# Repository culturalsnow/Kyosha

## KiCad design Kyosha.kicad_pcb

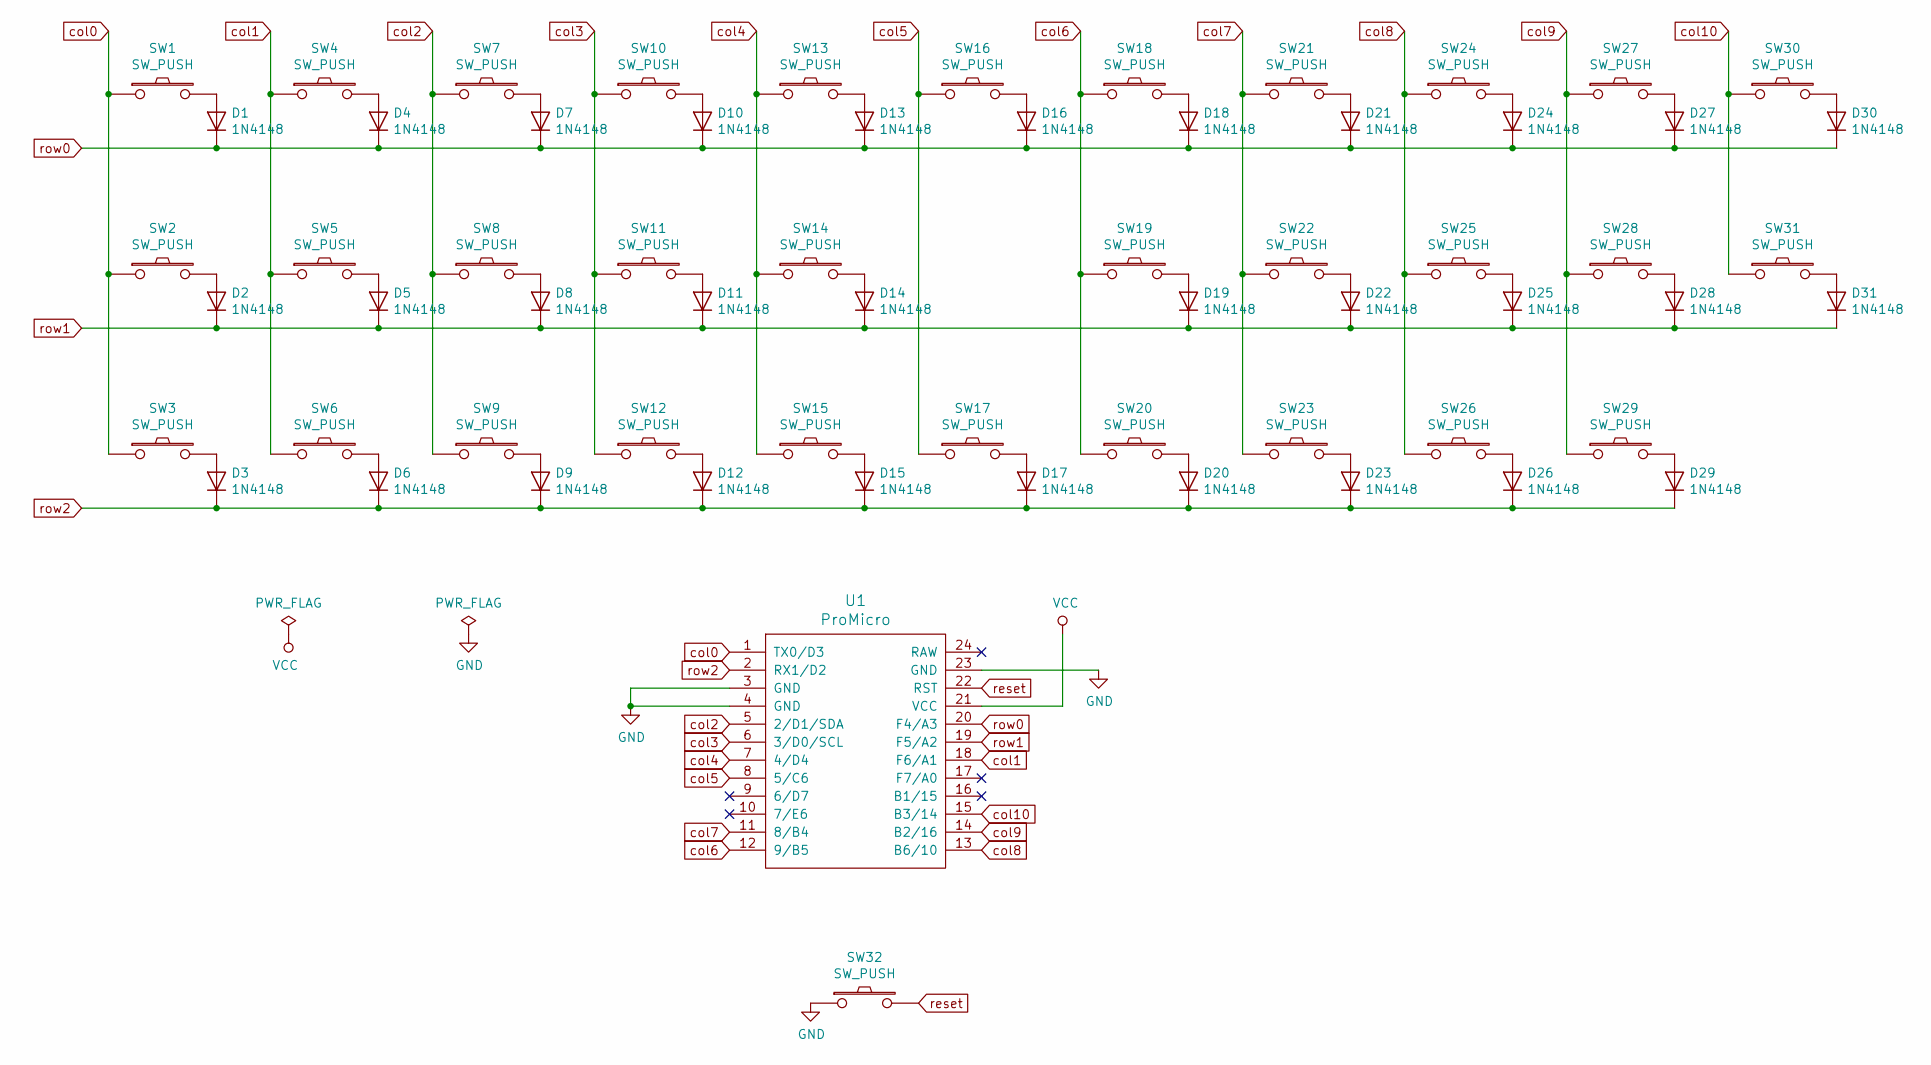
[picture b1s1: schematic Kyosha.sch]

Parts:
D1, D2, D3, D4, D5, D6, D7, D8, D9, D10, D11, D12, D13, D14, D15, D16, D17, D18, D19, D20, D21, D22, D23, D24, D25, D26, D27, D28, D29, D30, D31: 1N4148; D_SOD-123
SW1, SW2, SW3, SW4, SW5, SW6, SW7, SW8, SW9, SW10, SW11, SW12, SW13, SW14, SW15, SW16, SW17, SW18, SW19, SW20, SW21, SW22, SW23, SW24, SW25, SW26, SW27, SW28, SW30: SW_PUSH; SW_Cherry_MX_1.00u_PCB
SW29: SW_PUSH; SW_Cherry_MX_1.25u_PCB
SW31: SW_PUSH; SW_Cherry_MX_ISOEnter_PCB
SW32: SW_PUSH; ResetSW
U1: ProMicro; ProMicro_v2_Backside

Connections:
GND: SW32.1, U1.3 (GND), U1.4 (GND), U1.23 (GND)
unnamed: D1.2 (A), SW1.2
unnamed: D2.2 (A), SW2.2
unnamed: D3.2 (A), SW3.2
unnamed: D4.2 (A), SW4.2
unnamed: D5.2 (A), SW5.2
unnamed: D6.2 (A), SW6.2
unnamed: D7.2 (A), SW7.2
unnamed: D8.2 (A), SW8.2
unnamed: D9.2 (A), SW9.2
unnamed: D10.2 (A), SW10.2
unnamed: D11.2 (A), SW11.2
unnamed: D12.2 (A), SW12.2
unnamed: D13.2 (A), SW13.2
unnamed: D14.2 (A), SW14.2
unnamed: D15.2 (A), SW15.2
unnamed: D16.2 (A), SW16.2
unnamed: D17.2 (A), SW17.2
unnamed: D18.2 (A), SW18.2
unnamed: D19.2 (A), SW19.2
unnamed: D20.2 (A), SW20.2
unnamed: D21.2 (A), SW21.2
unnamed: D22.2 (A), SW22.2
unnamed: D23.2 (A), SW23.2
unnamed: D24.2 (A), SW24.2
unnamed: D25.2 (A), SW25.2
unnamed: D26.2 (A), SW26.2
unnamed: D27.2 (A), SW27.2
unnamed: D28.2 (A), SW28.2
unnamed: D29.2 (A), SW29.2
unnamed: D30.2 (A), SW30.2
unnamed: D31.2 (A), SW31.2
VCC: U1.21 (VCC)
col0: SW1.1, SW2.1, SW3.1, U1.1 (TX0/D3)
col1: SW4.1, SW5.1, SW6.1, U1.18 (F6/A1)
col2: SW7.1, SW8.1, SW9.1, U1.5 (2/D1/SDA)
col3: SW10.1, SW11.1, SW12.1, U1.6 (3/D0/SCL)
col4: SW13.1, SW14.1, SW15.1, U1.7 (4/D4)
col5: SW16.1, SW17.1, U1.8 (5/C6)
col6: SW18.1, SW19.1, SW20.1, U1.12 (9/B5)
col7: SW21.1, SW22.1, SW23.1, U1.11 (8/B4)
col8: SW24.1, SW25.1, SW26.1, U1.13 (B6/10)
col9: SW27.1, SW28.1, SW29.1, U1.14 (B2/16)
col10: SW30.1, SW31.1, U1.15 (B3/14)
reset: SW32.2, U1.22 (RST)
row0: D1.1 (K), D4.1 (K), D7.1 (K), D10.1 (K), D13.1 (K), D16.1 (K), D18.1 (K), D21.1 (K), D24.1 (K), D27.1 (K), D30.1 (K), U1.20 (F4/A3)
row1: D2.1 (K), D5.1 (K), D8.1 (K), D11.1 (K), D14.1 (K), D19.1 (K), D22.1 (K), D25.1 (K), D28.1 (K), D31.1 (K), U1.19 (F5/A2)
row2: D3.1 (K), D6.1 (K), D9.1 (K), D12.1 (K), D15.1 (K), D17.1 (K), D20.1 (K), D23.1 (K), D26.1 (K), D29.1 (K), U1.2 (RX1/D2)

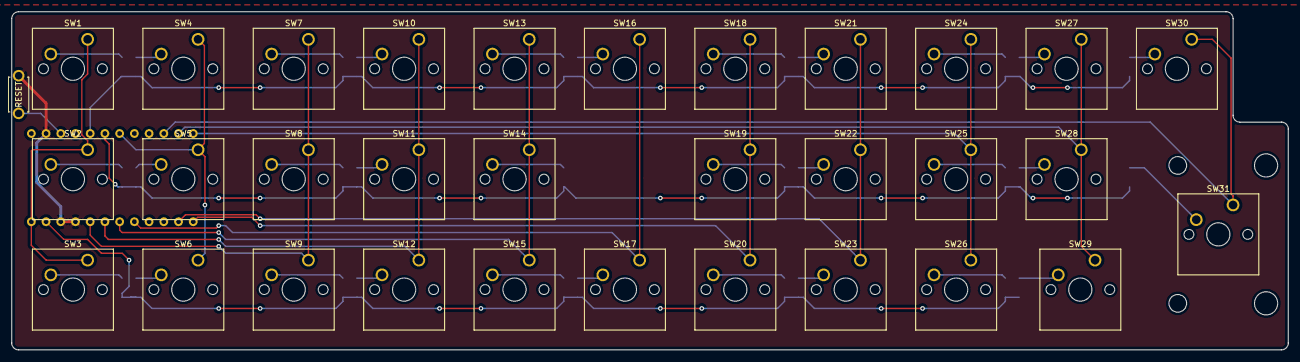
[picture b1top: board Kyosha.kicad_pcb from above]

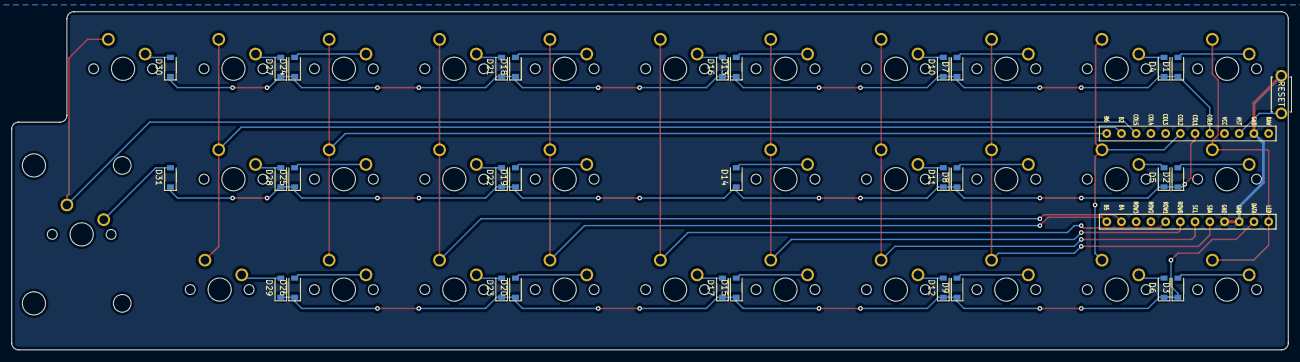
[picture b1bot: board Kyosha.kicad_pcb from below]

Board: 2 copper layers, 220.3 x 58.3 mm, 64 parts (32 on the bottom side), 47 nets.

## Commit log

2019-05-18 PCB in progress
2019-05-19 pcb first pass
